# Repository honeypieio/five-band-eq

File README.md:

# Five-band EQ
Preamp and five-band EQ for guitar amplifiers

The goal of this project is to create a simple guitar amplifier frontend using commonly available components

The PCB is single-sided and was created using Kicad. It is optimised for home etching - chunky traces, generous ground plane clearance

Key specifications:

* Requires a +/-15V power supply
* ~80mA quiescent current draw
* Adjustable input gain and attenuation
* Hard clipping diodes for distortion
* Five-band EQ - bass, middle, treble, presence, brilliance
* EQ 6dB boost/cut

To build the project, everything needed is inside the `docs` directory

* PCB layout
* Bill of materials
* Silkscreen
* Schematics

An LTspice simulation is also available in the `simulation` directory

---

### To-do

* Add EQ alignment process instructions

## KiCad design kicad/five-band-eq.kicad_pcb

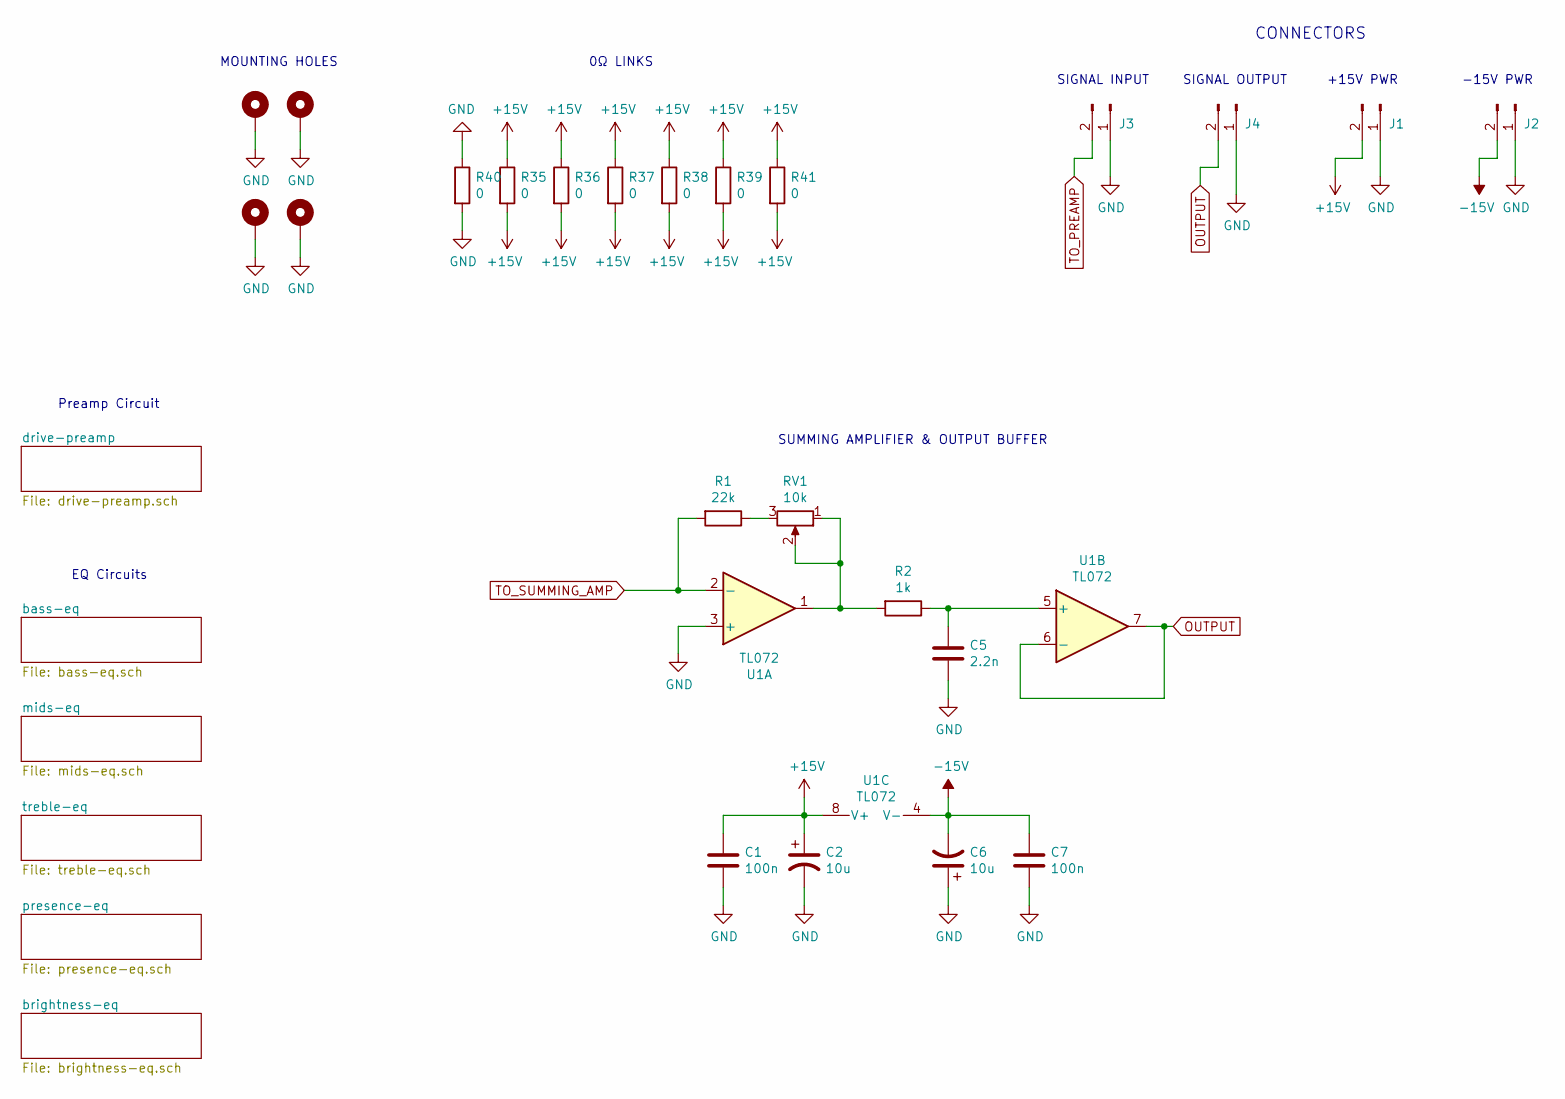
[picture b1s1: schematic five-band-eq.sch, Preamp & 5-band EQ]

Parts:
C1, C7: 100n; C_Disc_D7.0mm_W2.5mm_P5.00mm
C2, C6: 10u; CP_Radial_D5.0mm_P2.50mm
C5: 2.2n; C_Disc_D3.8mm_W2.6mm_P2.50mm
H1, H2, H3, H4: MountingHole_Pad; MountingHole_3.2mm_M3_DIN965_Pad
J1, J2, J4: Conn_01x02_Male; Molex_KK-254_AE-6410-02A_1x02_P2.54mm_Vertical
J3: Conn_01x02_Male; PinHeader_1x02_P2.54mm_Vertical
R1: 22k; R_Axial_DIN0207_L6.3mm_D2.5mm_P2.54mm_Vertical
R2: 1k; R_Axial_DIN0207_L6.3mm_D2.5mm_P2.54mm_Vertical
R35, R36, R37, R38, R39, R40, R41: 0; R_Axial_DIN0207_L6.3mm_D2.5mm_P10.16mm_Horizontal
RV1: 10k; Potentiometer_Runtron_RM-065_Vertical
U1: TL072; DIP-8_W7.62mm_LongPads

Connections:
+15V: C1.1, C2.1, J1.2, R35.1, R35.2, R36.1, R36.2, R37.1, R37.2, R38.1, R38.2, R39.1, R39.2, R41.1, R41.2, U1.8 (V+); also elsewhere on the board
-15V: C6.2, C7.1, J2.2, U1.4 (V-); also elsewhere on the board
GND: C1.2, C2.2, C5.2, C6.1, C7.2, H1.1, H2.1, H3.1, H4.1, J1.1, J2.1, J3.1, J4.1, R40.1, R40.2, U1.3 (+); also elsewhere on the board
unnamed: C5.1, R2.1, U1.5 (+)
unnamed: R1.1, RV1.3
unnamed: R2.2, RV1.1, RV1.2, U1.1
OUTPUT: J4.2, U1.6 (-), U1.7
TO_PREAMP: J3.2; also elsewhere on the board
TO_SUMMING_AMP: R1.2, U1.2 (-); also elsewhere on the board

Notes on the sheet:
0Ω LINKS
MOUNTING HOLES
SIGNAL INPUT
SIGNAL OUTPUT
+15V PWR
-15V PWR
CONNECTORS
SUMMING AMPLIFIER & OUTPUT BUFFER
EQ Circuits
Preamp Circuit

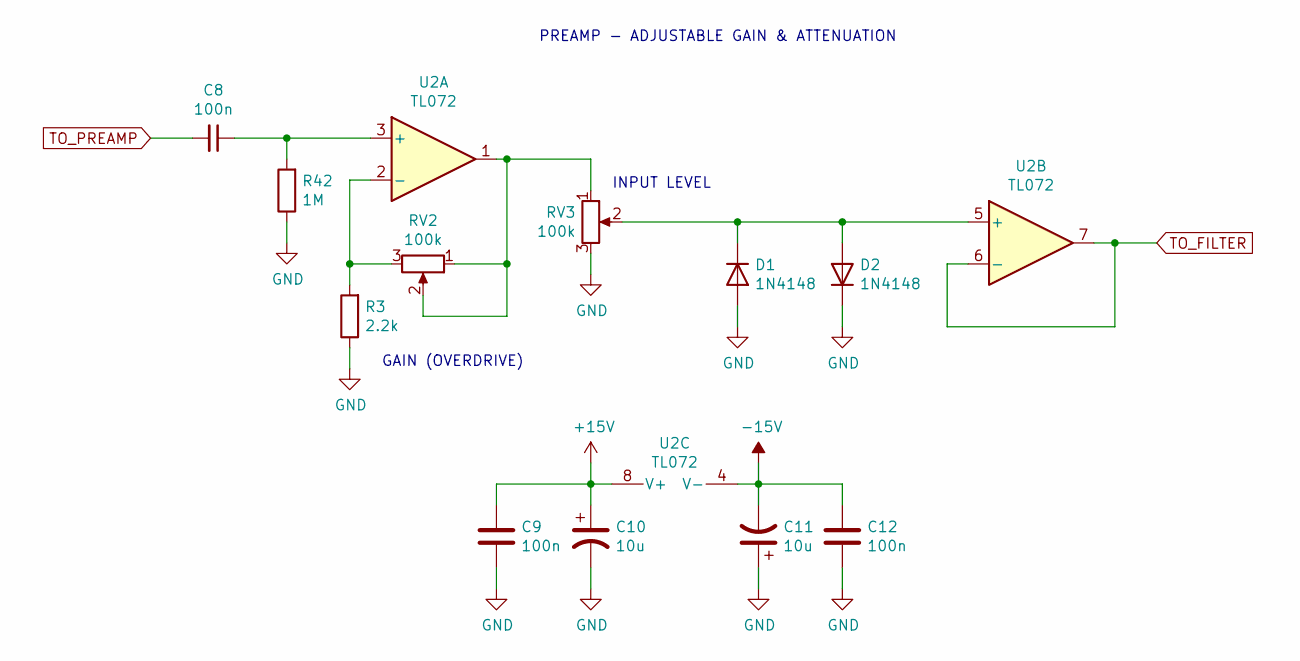
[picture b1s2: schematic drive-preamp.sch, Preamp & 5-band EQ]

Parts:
C8, C9, C12: 100n; C_Disc_D7.0mm_W2.5mm_P5.00mm
C10, C11: 10u; CP_Radial_D5.0mm_P2.50mm
D1, D2: 1N4148; D_DO-35_SOD27_P7.62mm_Horizontal
R3: 2.2k; R_Axial_DIN0207_L6.3mm_D2.5mm_P2.54mm_Vertical
R42: 1M; R_Axial_DIN0207_L6.3mm_D2.5mm_P2.54mm_Vertical
RV2, RV3: 100k; PinHeader_1x03_P2.54mm_Vertical
U2: TL072; DIP-8_W7.62mm_LongPads

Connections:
+15V: C9.1, C10.1, U2.8 (V+); also elsewhere on the board
-15V: C11.2, C12.1, U2.4 (V-); also elsewhere on the board
GND: C9.2, C10.2, C11.1, C12.2, D1.2 (A), D2.1 (K), R3.1, R42.1, RV3.3; also elsewhere on the board
unnamed: C8.1, R42.2, U2.3 (+)
unnamed: D1.1 (K), D2.2 (A), RV3.2, U2.5 (+)
unnamed: R3.2, RV2.3, U2.2 (-)
unnamed: RV2.1, RV2.2, RV3.1, U2.1
TO_FILTER: U2.6 (-), U2.7; also elsewhere on the board
TO_PREAMP: C8.2; also elsewhere on the board

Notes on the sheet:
GAIN (OVERDRIVE)
INPUT LEVEL
PREAMP - ADJUSTABLE GAIN & ATTENUATION

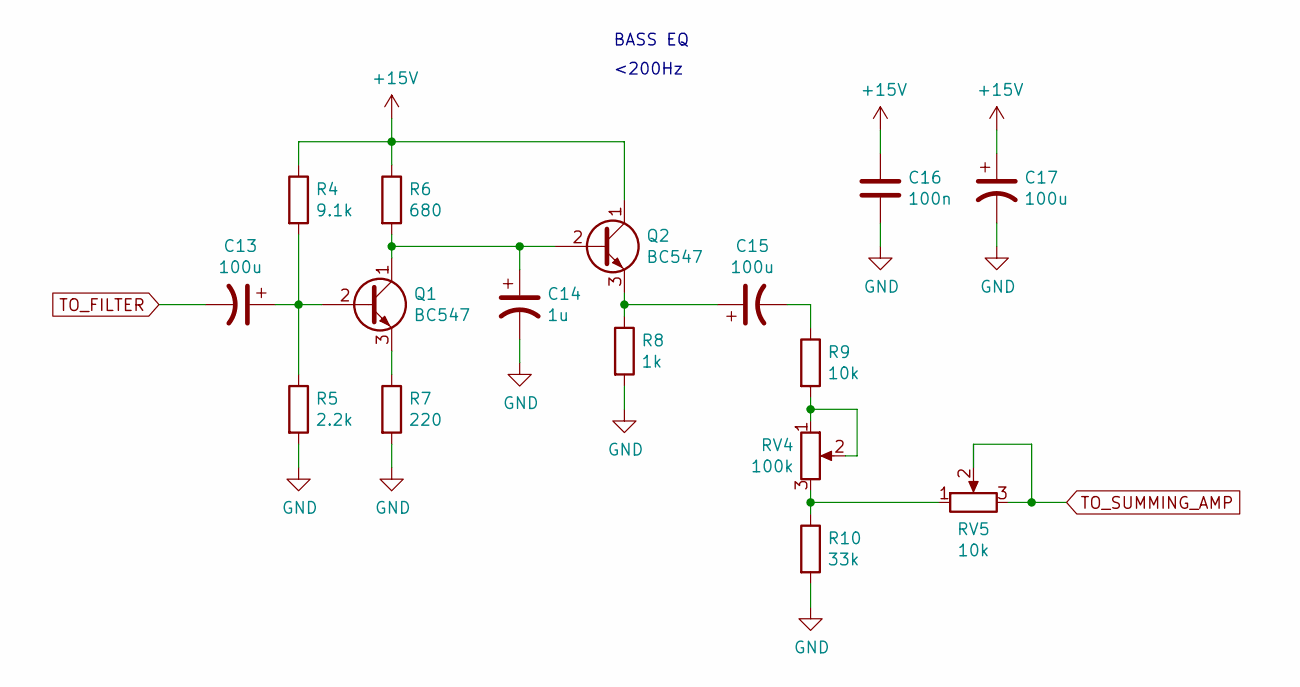
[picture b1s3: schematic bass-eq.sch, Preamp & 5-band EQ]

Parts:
C13, C15, C17: 100u; CP_Radial_D6.3mm_P2.50mm
C14: 1u; C_Disc_D7.5mm_W5.0mm_P5.00mm
C16: 100n; C_Disc_D7.0mm_W2.5mm_P5.00mm
Q1, Q2: BC547; TO-92_Inline_Wide
R4: 9.1k; R_Axial_DIN0207_L6.3mm_D2.5mm_P2.54mm_Vertical
R5: 2.2k; R_Axial_DIN0207_L6.3mm_D2.5mm_P2.54mm_Vertical
R6: 680; R_Axial_DIN0207_L6.3mm_D2.5mm_P2.54mm_Vertical
R7: 220; R_Axial_DIN0207_L6.3mm_D2.5mm_P2.54mm_Vertical
R8: 1k; R_Axial_DIN0207_L6.3mm_D2.5mm_P2.54mm_Vertical
R9: 10k; R_Axial_DIN0207_L6.3mm_D2.5mm_P2.54mm_Vertical
R10: 33k; R_Axial_DIN0207_L6.3mm_D2.5mm_P2.54mm_Vertical
RV4: 100k; PinHeader_1x03_P2.54mm_Vertical
RV5: 10k; Potentiometer_Runtron_RM-065_Vertical

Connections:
+15V: C16.1, C17.1, Q2.1 (C), R4.1, R6.1; also elsewhere on the board
GND: C14.2, C16.2, C17.2, R5.2, R7.2, R8.2, R10.2; also elsewhere on the board
unnamed: C13.1, Q1.2 (B), R4.2, R5.1
unnamed: C14.1, Q1.1 (C), Q2.2 (B), R6.2
unnamed: C15.1, Q2.3 (E), R8.1
unnamed: C15.2, R9.1
unnamed: Q1.3 (E), R7.1
unnamed: R9.2, RV4.1, RV4.2
unnamed: R10.1, RV4.3, RV5.1
TO_FILTER: C13.2; also elsewhere on the board
TO_SUMMING_AMP: RV5.2, RV5.3; also elsewhere on the board

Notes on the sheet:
BASS EQ
<200Hz

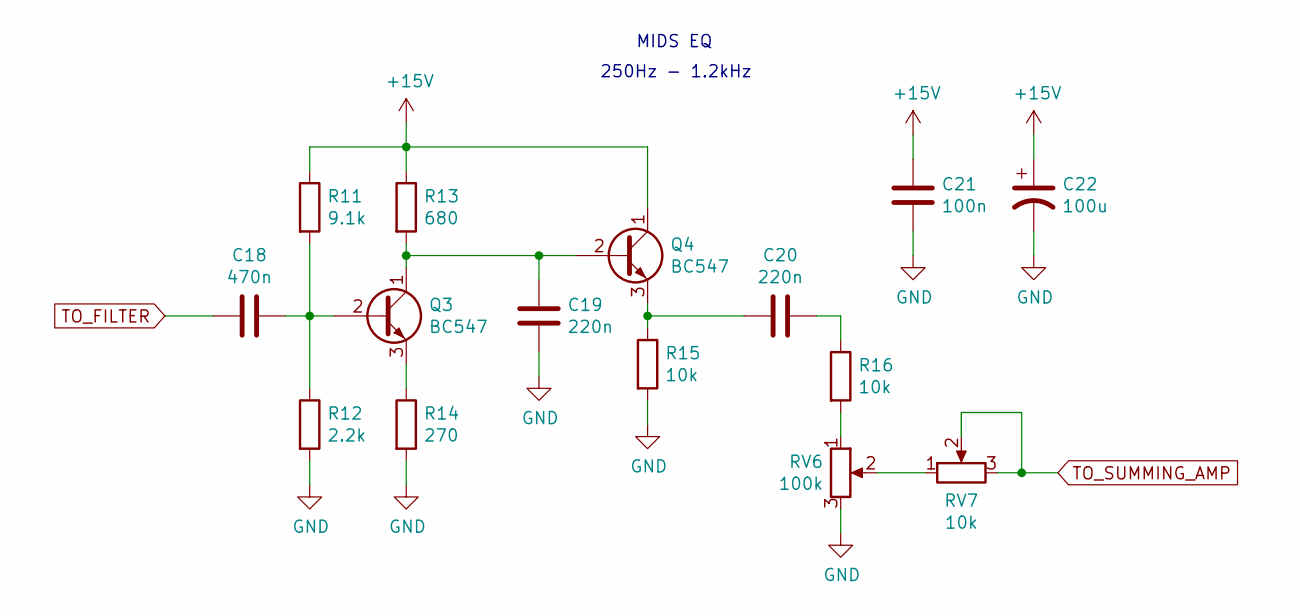
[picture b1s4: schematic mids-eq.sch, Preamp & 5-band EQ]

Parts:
C18: 470n; C_Disc_D7.5mm_W4.4mm_P5.00mm
C19, C20: 220n; C_Disc_D7.5mm_W2.5mm_P5.00mm
C21: 100n; C_Disc_D7.0mm_W2.5mm_P5.00mm
C22: 100u; CP_Radial_D6.3mm_P2.50mm
Q3, Q4: BC547; TO-92_Inline_Wide
R11: 9.1k; R_Axial_DIN0207_L6.3mm_D2.5mm_P2.54mm_Vertical
R12: 2.2k; R_Axial_DIN0207_L6.3mm_D2.5mm_P2.54mm_Vertical
R13: 680; R_Axial_DIN0207_L6.3mm_D2.5mm_P2.54mm_Vertical
R14: 270; R_Axial_DIN0207_L6.3mm_D2.5mm_P2.54mm_Vertical
R15, R16: 10k; R_Axial_DIN0207_L6.3mm_D2.5mm_P2.54mm_Vertical
RV6: 100k; PinHeader_1x03_P2.54mm_Vertical
RV7: 10k; Potentiometer_Runtron_RM-065_Vertical

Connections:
+15V: C21.1, C22.1, Q4.1 (C), R11.1, R13.1; also elsewhere on the board
GND: C19.2, C21.2, C22.2, R12.2, R14.2, R15.2, RV6.3; also elsewhere on the board
unnamed: C18.1, Q3.2 (B), R11.2, R12.1
unnamed: C19.1, Q3.1 (C), Q4.2 (B), R13.2
unnamed: C20.1, R16.1
unnamed: C20.2, Q4.3 (E), R15.1
unnamed: Q3.3 (E), R14.1
unnamed: R16.2, RV6.1
unnamed: RV6.2, RV7.1
TO_FILTER: C18.2; also elsewhere on the board
TO_SUMMING_AMP: RV7.2, RV7.3; also elsewhere on the board

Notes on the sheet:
MIDS EQ
250Hz - 1.2kHz

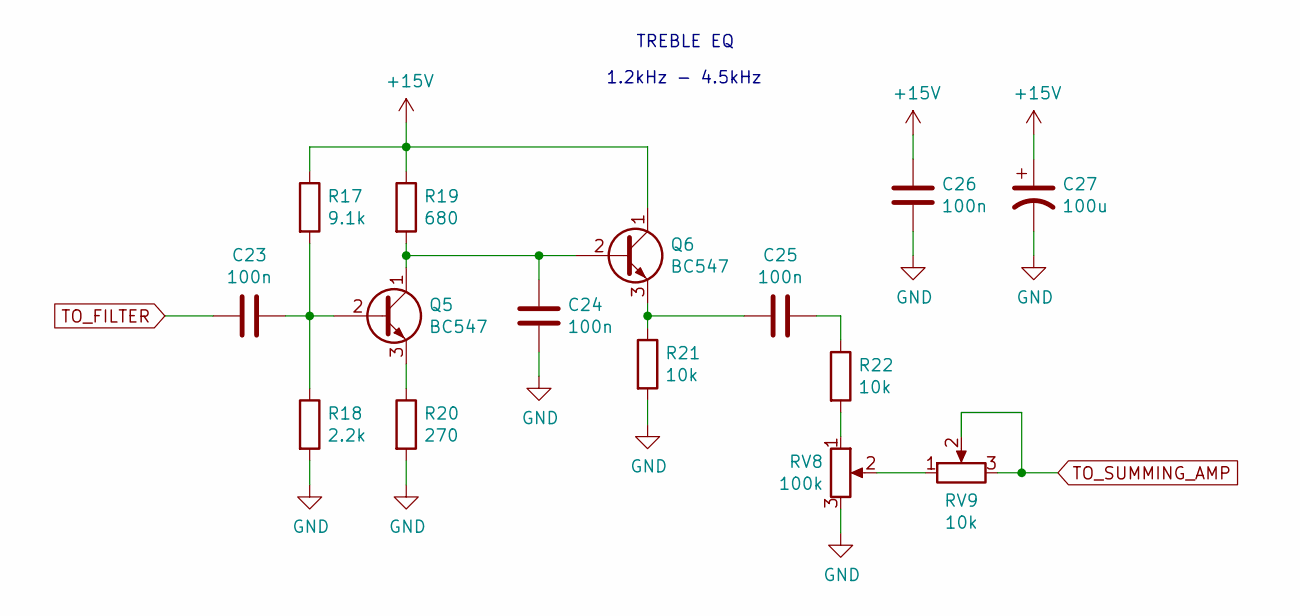
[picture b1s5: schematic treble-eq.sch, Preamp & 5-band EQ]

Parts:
C23, C24, C25, C26: 100n; C_Disc_D7.0mm_W2.5mm_P5.00mm
C27: 100u; CP_Radial_D6.3mm_P2.50mm
Q5, Q6: BC547; TO-92_Inline_Wide
R17: 9.1k; R_Axial_DIN0207_L6.3mm_D2.5mm_P2.54mm_Vertical
R18: 2.2k; R_Axial_DIN0207_L6.3mm_D2.5mm_P2.54mm_Vertical
R19: 680; R_Axial_DIN0207_L6.3mm_D2.5mm_P2.54mm_Vertical
R20: 270; R_Axial_DIN0207_L6.3mm_D2.5mm_P2.54mm_Vertical
R21, R22: 10k; R_Axial_DIN0207_L6.3mm_D2.5mm_P2.54mm_Vertical
RV8: 100k; PinHeader_1x03_P2.54mm_Vertical
RV9: 10k; Potentiometer_Runtron_RM-065_Vertical

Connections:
+15V: C26.1, C27.1, Q6.1 (C), R17.1, R19.1; also elsewhere on the board
GND: C24.2, C26.2, C27.2, R18.2, R20.2, R21.2, RV8.3; also elsewhere on the board
unnamed: C23.1, Q5.2 (B), R17.2, R18.1
unnamed: C24.1, Q5.1 (C), Q6.2 (B), R19.2
unnamed: C25.1, R22.1
unnamed: C25.2, Q6.3 (E), R21.1
unnamed: Q5.3 (E), R20.1
unnamed: R22.2, RV8.1
unnamed: RV8.2, RV9.1
TO_FILTER: C23.2; also elsewhere on the board
TO_SUMMING_AMP: RV9.2, RV9.3; also elsewhere on the board

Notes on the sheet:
TREBLE EQ
1.2kHz - 4.5kHz

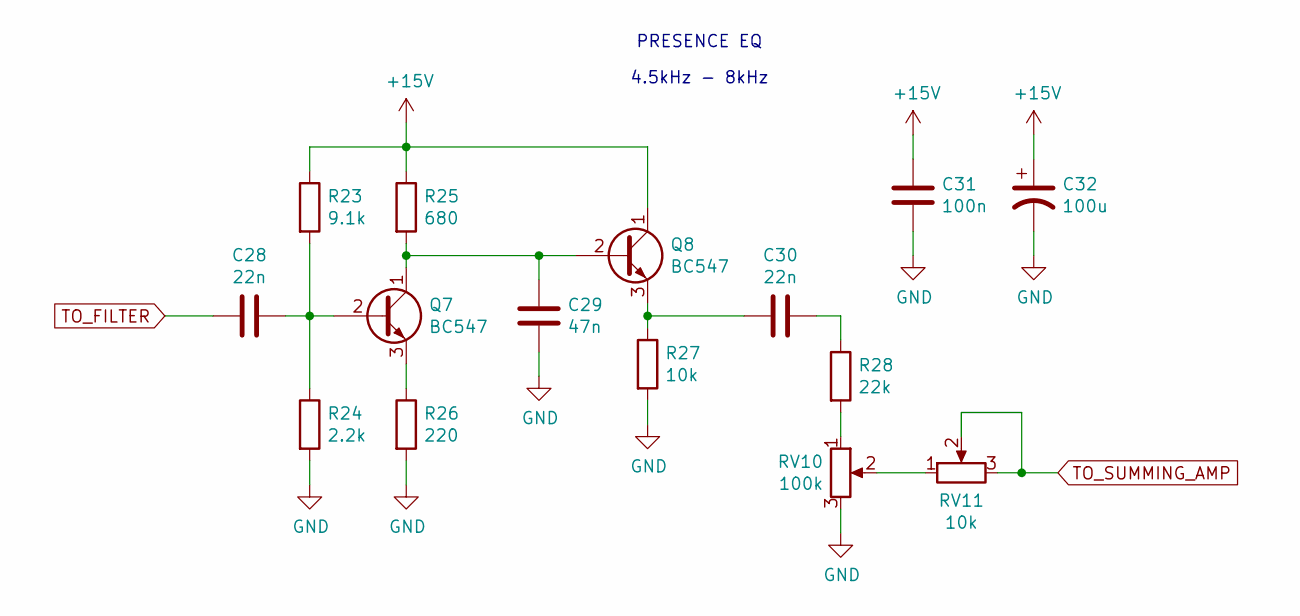
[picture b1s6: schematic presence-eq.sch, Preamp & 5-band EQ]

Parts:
C28, C30: 22n; C_Disc_D7.5mm_W2.5mm_P5.00mm
C29: 47n; C_Disc_D4.3mm_W1.9mm_P5.00mm
C31: 100n; C_Disc_D7.0mm_W2.5mm_P5.00mm
C32: 100u; CP_Radial_D6.3mm_P2.50mm
Q7, Q8: BC547; TO-92_Inline_Wide
R23: 9.1k; R_Axial_DIN0207_L6.3mm_D2.5mm_P2.54mm_Vertical
R24: 2.2k; R_Axial_DIN0207_L6.3mm_D2.5mm_P2.54mm_Vertical
R25: 680; R_Axial_DIN0207_L6.3mm_D2.5mm_P2.54mm_Vertical
R26: 220; R_Axial_DIN0207_L6.3mm_D2.5mm_P2.54mm_Vertical
R27: 10k; R_Axial_DIN0207_L6.3mm_D2.5mm_P2.54mm_Vertical
R28: 22k; R_Axial_DIN0207_L6.3mm_D2.5mm_P2.54mm_Vertical
RV10: 100k; PinHeader_1x03_P2.54mm_Vertical
RV11: 10k; Potentiometer_Runtron_RM-065_Vertical

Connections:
+15V: C31.1, C32.1, Q8.1 (C), R23.1, R25.1; also elsewhere on the board
GND: C29.2, C31.2, C32.2, R24.2, R26.2, R27.2, RV10.3; also elsewhere on the board
unnamed: C28.1, Q7.2 (B), R23.2, R24.1
unnamed: C29.1, Q7.1 (C), Q8.2 (B), R25.2
unnamed: C30.1, R28.1
unnamed: C30.2, Q8.3 (E), R27.1
unnamed: Q7.3 (E), R26.1
unnamed: R28.2, RV10.1
unnamed: RV10.2, RV11.1
TO_FILTER: C28.2; also elsewhere on the board
TO_SUMMING_AMP: RV11.2, RV11.3; also elsewhere on the board

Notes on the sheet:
PRESENCE EQ
4.5kHz - 8kHz

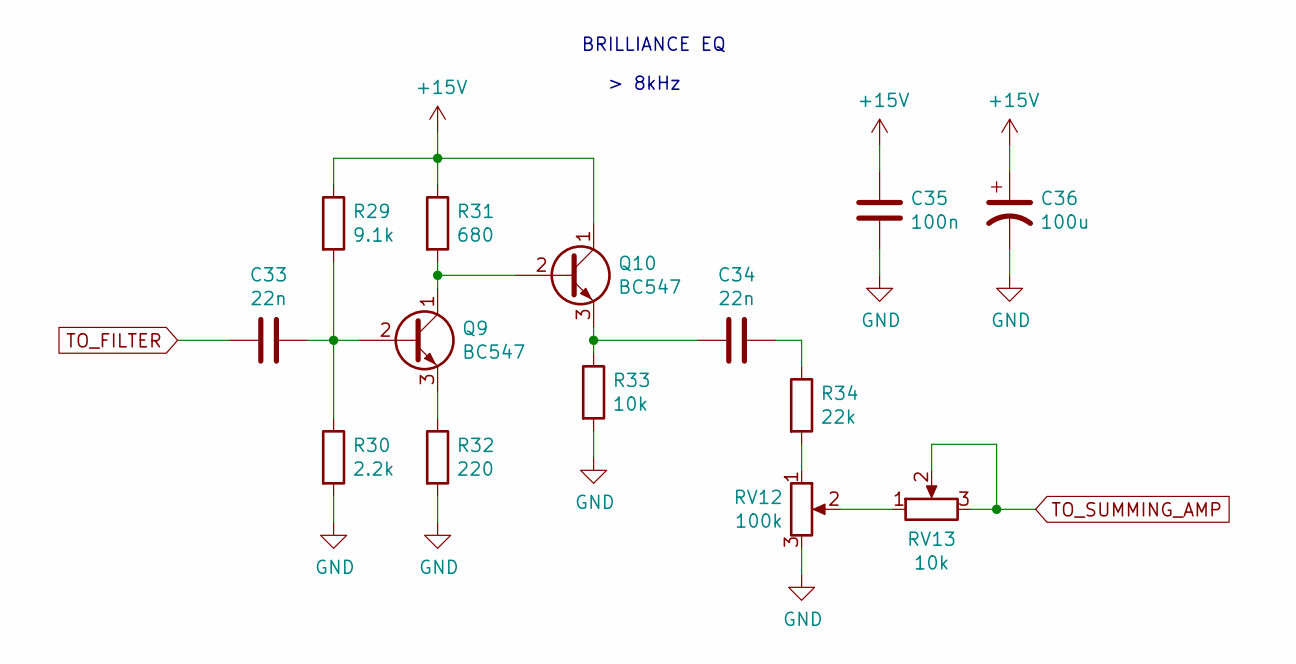
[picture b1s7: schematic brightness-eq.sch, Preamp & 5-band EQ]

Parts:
C33, C34: 22n; C_Disc_D7.5mm_W2.5mm_P5.00mm
C35: 100n; C_Disc_D7.0mm_W2.5mm_P5.00mm
C36: 100u; CP_Radial_D6.3mm_P2.50mm
Q9, Q10: BC547; TO-92_Inline_Wide
R29: 9.1k; R_Axial_DIN0207_L6.3mm_D2.5mm_P2.54mm_Vertical
R30: 2.2k; R_Axial_DIN0207_L6.3mm_D2.5mm_P2.54mm_Vertical
R31: 680; R_Axial_DIN0207_L6.3mm_D2.5mm_P2.54mm_Vertical
R32: 220; R_Axial_DIN0207_L6.3mm_D2.5mm_P2.54mm_Vertical
R33: 10k; R_Axial_DIN0207_L6.3mm_D2.5mm_P2.54mm_Vertical
R34: 22k; R_Axial_DIN0207_L6.3mm_D2.5mm_P2.54mm_Vertical
RV12: 100k; PinHeader_1x03_P2.54mm_Vertical
RV13: 10k; Potentiometer_Runtron_RM-065_Vertical

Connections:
+15V: C35.1, C36.1, Q10.1 (C), R29.1, R31.1; also elsewhere on the board
GND: C35.2, C36.2, R30.2, R32.2, R33.2, RV12.3; also elsewhere on the board
unnamed: C33.1, Q9.2 (B), R29.2, R30.1
unnamed: C34.1, R34.1
unnamed: C34.2, Q10.3 (E), R33.1
unnamed: Q9.3 (E), R32.1
unnamed: Q9.1 (C), Q10.2 (B), R31.2
unnamed: R34.2, RV12.1
unnamed: RV12.2, RV13.1
TO_FILTER: C33.2; also elsewhere on the board
TO_SUMMING_AMP: RV13.2, RV13.3; also elsewhere on the board

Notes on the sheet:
BRILLIANCE EQ
> 8kHz

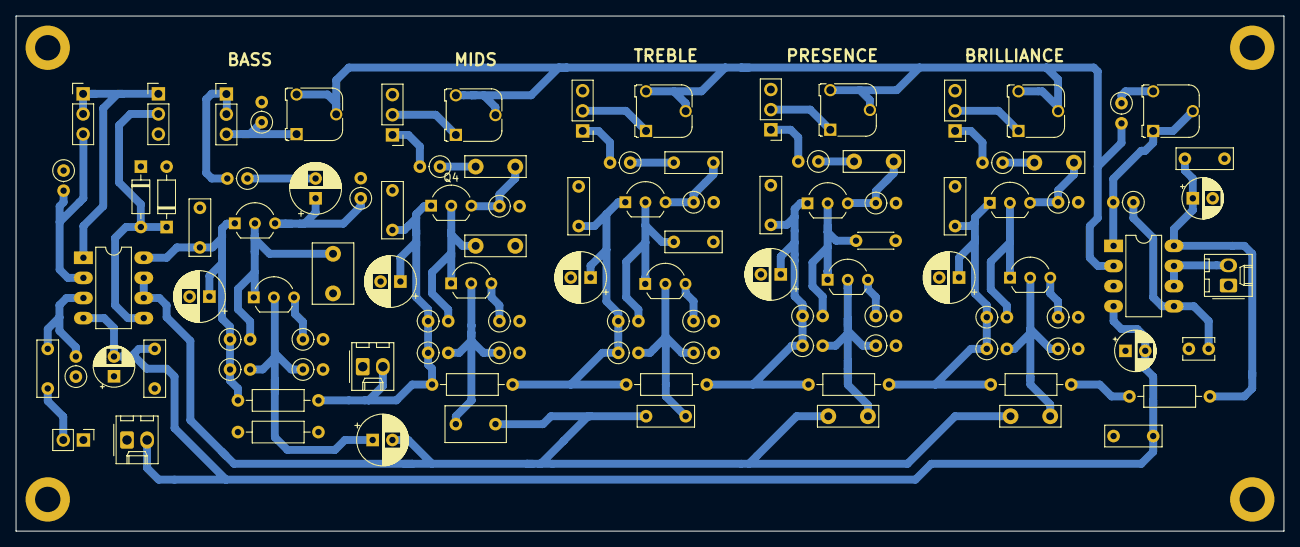
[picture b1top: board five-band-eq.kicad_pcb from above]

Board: 2 copper layers, 160.0 x 65.0 mm, 109 parts (0 on the bottom side), 49 nets.

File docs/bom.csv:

Qty,Reference(s),Value,LibPart,Footprint
12,"C1, C7, C9, C12, C16, C21, C23, C24, C25, C26, C31, C35",100n,Device:C,Capacitor_THT:C_Disc_D7.0mm_W2.5mm_P5.00mm
4,"C2, C6, C10, C11",10u,Device:CP1,Capacitor_THT:CP_Radial_D5.0mm_P2.50mm
1,C5,2.2n,Device:C,Capacitor_THT:C_Disc_D3.8mm_W2.6mm_P2.50mm
1,C8,100n,Device:C_Small,Capacitor_THT:C_Disc_D7.0mm_W2.5mm_P5.00mm
7,"C13, C15, C17, C22, C27, C32, C36",100u,Device:CP1,Capacitor_THT:CP_Radial_D6.3mm_P2.50mm
1,C14,1u,Device:CP1,Capacitor_THT:C_Disc_D7.5mm_W5.0mm_P5.00mm
1,C18,470n,Device:C,Capacitor_THT:C_Disc_D7.5mm_W4.4mm_P5.00mm
2,"C19, C20",220n,Device:C,Capacitor_THT:C_Disc_D7.5mm_W2.5mm_P5.00mm
4,"C28, C30, C33, C34",22n,Device:C,Capacitor_THT:C_Disc_D7.5mm_W2.5mm_P5.00mm
1,C29,47n,Device:C,Capacitor_THT:C_Disc_D4.3mm_W1.9mm_P5.00mm
2,"D1, D2",1N4148,Diode:1N4148,Diode_THT:D_DO-35_SOD27_P7.62mm_Horizontal
3,"J1, J2, J4",Conn_01x02_Male,Connector:Conn_01x02_Male,Connector_Molex:Molex_KK-254_AE-6410-02A_1x02_P2.54mm_Vertical
1,J3,Conn_01x02_Male,Connector:Conn_01x02_Male,Connector_PinHeader_2.54mm:PinHeader_1x02_P2.54mm_Vertical
10,"Q1, Q2, Q3, Q4, Q5, Q6, Q7, Q8, Q9, Q10",BC547,Transistor_BJT:BC547,Package_TO_SOT_THT:TO-92_Inline_Wide
3,"R1, R28, R34",22k,Device:R,Resistor_THT:R_Axial_DIN0207_L6.3mm_D2.5mm_P2.54mm_Vertical
2,"R2, R8",1k,Device:R,Resistor_THT:R_Axial_DIN0207_L6.3mm_D2.5mm_P2.54mm_Vertical
6,"R3, R5, R12, R18, R24, R30",2.2k,Device:R,Resistor_THT:R_Axial_DIN0207_L6.3mm_D2.5mm_P2.54mm_Vertical
5,"R4, R11, R17, R23, R29",9.1k,Device:R,Resistor_THT:R_Axial_DIN0207_L6.3mm_D2.5mm_P2.54mm_Vertical
5,"R6, R13, R19, R25, R31",680,Device:R,Resistor_THT:R_Axial_DIN0207_L6.3mm_D2.5mm_P2.54mm_Vertical
3,"R7, R26, R32",220,Device:R,Resistor_THT:R_Axial_DIN0207_L6.3mm_D2.5mm_P2.54mm_Vertical
7,"R9, R15, R16, R21, R22, R27, R33",10k,Device:R,Resistor_THT:R_Axial_DIN0207_L6.3mm_D2.5mm_P2.54mm_Vertical
1,R10,33k,Device:R,Resistor_THT:R_Axial_DIN0207_L6.3mm_D2.5mm_P2.54mm_Vertical
2,"R14, R20",270,Device:R,Resistor_THT:R_Axial_DIN0207_L6.3mm_D2.5mm_P2.54mm_Vertical
7,"R35, R36, R37, R38, R39, R40, R41",0,Device:R,Resistor_THT:R_Axial_DIN0207_L6.3mm_D2.5mm_P10.16mm_Horizontal
1,R42,1M,Device:R,Resistor_THT:R_Axial_DIN0207_L6.3mm_D2.5mm_P2.54mm_Vertical
6,"RV1, RV5, RV7, RV9, RV11, RV13",10k,Device:R_POT,Potentiometer_THT:Potentiometer_Runtron_RM-065_Vertical
2,"RV2, RV3",100k Logarithmic,Device:R_POT,Connector_PinHeader_2.54mm:PinHeader_1x03_P2.54mm_Vertical
5,"RV4, RV6, RV8, RV10, RV12",100k Linear,Device:R_POT,Connector_PinHeader_2.54mm:PinHeader_1x03_P2.54mm_Vertical
2,"U1, U2",TL072,Amplifier_Operational:TL072,Package_DIP:DIP-8_W7.62mm_LongPads

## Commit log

2022-06-26 Revision A
2022-06-26 Added LTSpice simulation files
2022-06-26 Added image of constructed PCB
2022-06-26 Added documentation banner
2022-06-26 Fixed documentation banner
